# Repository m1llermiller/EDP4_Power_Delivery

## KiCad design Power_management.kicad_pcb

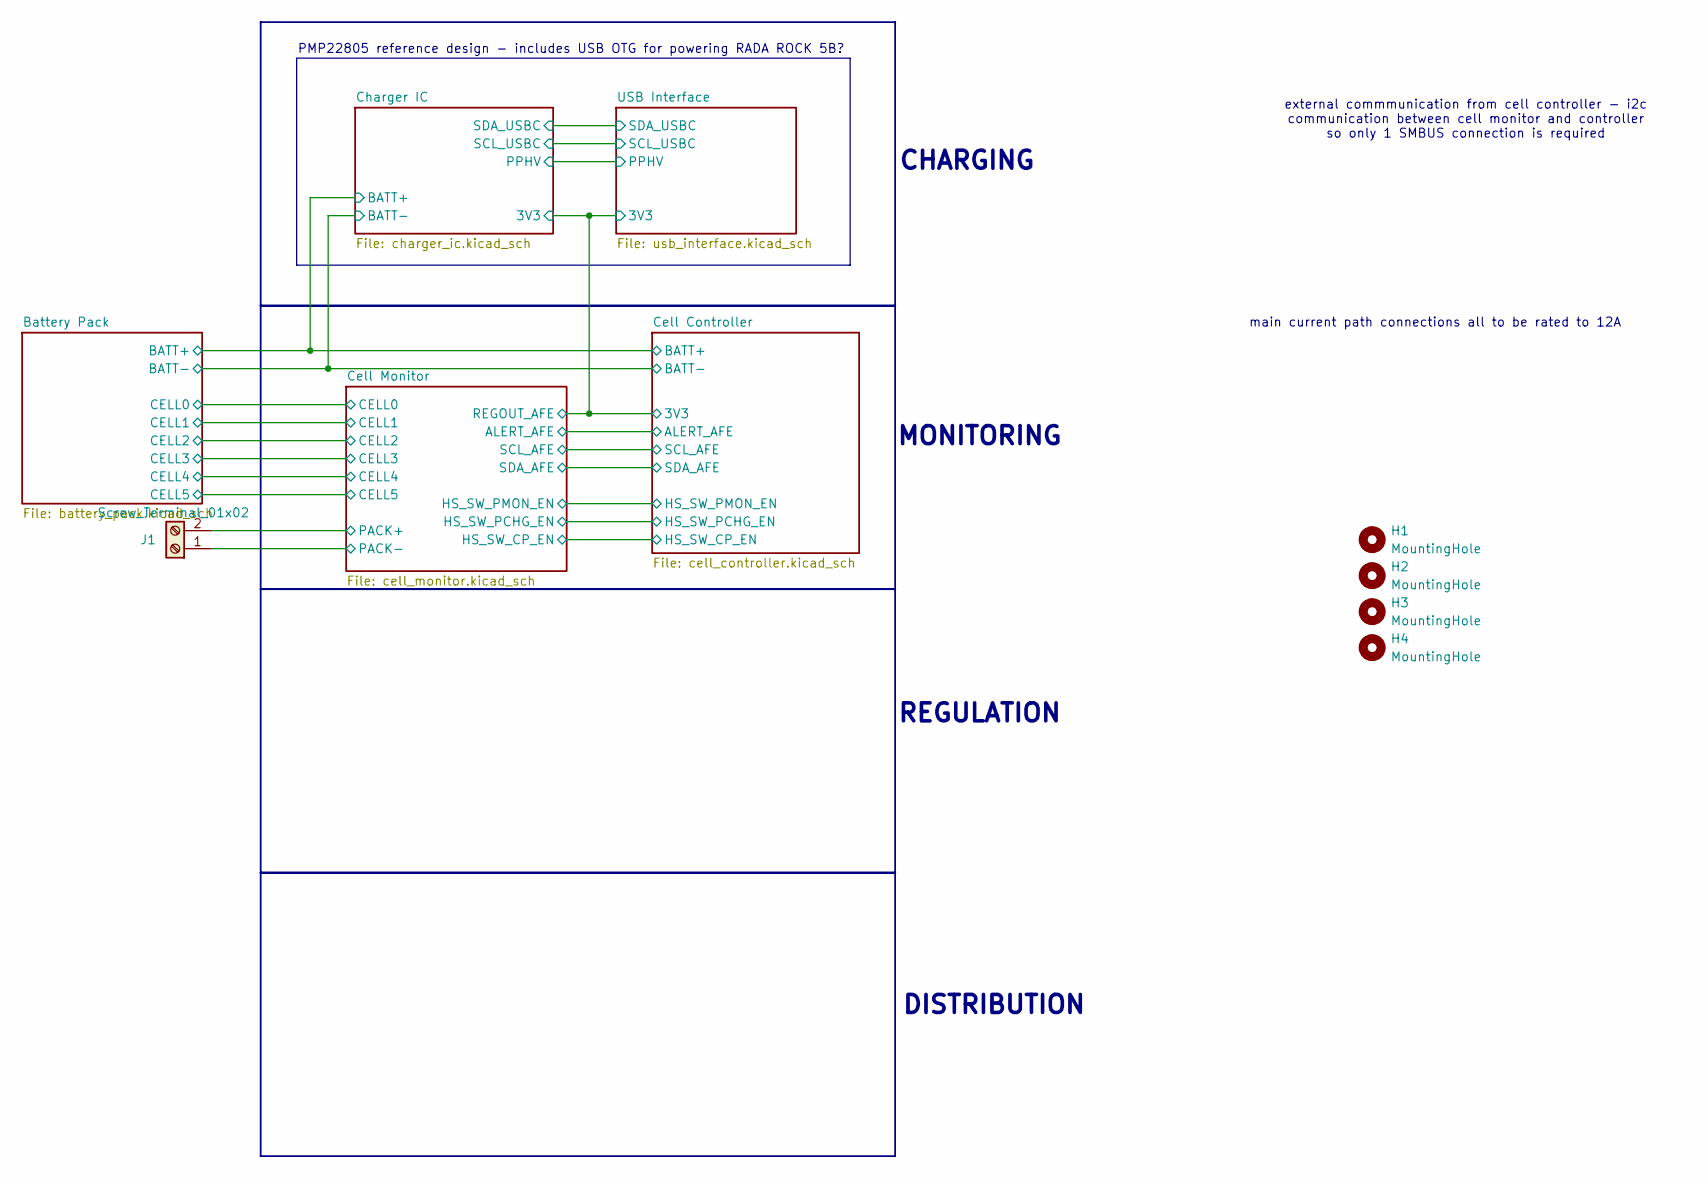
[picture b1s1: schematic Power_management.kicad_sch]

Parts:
H1, H2, H3, H4: MountingHole; MountingHole_3.2mm_M3
J1: Screw_Terminal_01x02; TerminalBlock_Phoenix_MKDS-1,5-2-5.08_1x02_P5.08mm_Horizont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

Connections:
/Cell Monitor/PACK+: J1.2; also elsewhere on the board
/Cell Monitor/PACK-: J1.1; also elsewhere on the board

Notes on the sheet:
external commmunication from cell controller - i2c communication between cell monitor and controller so only 1 SMBUS connection is required
CHARGING
REGULATION
MONITORING
PMP22805 reference design - includes USB OTG for powering RADA ROCK 5B?
DISTRIBUTION
main current path connections all to be rated to 12A

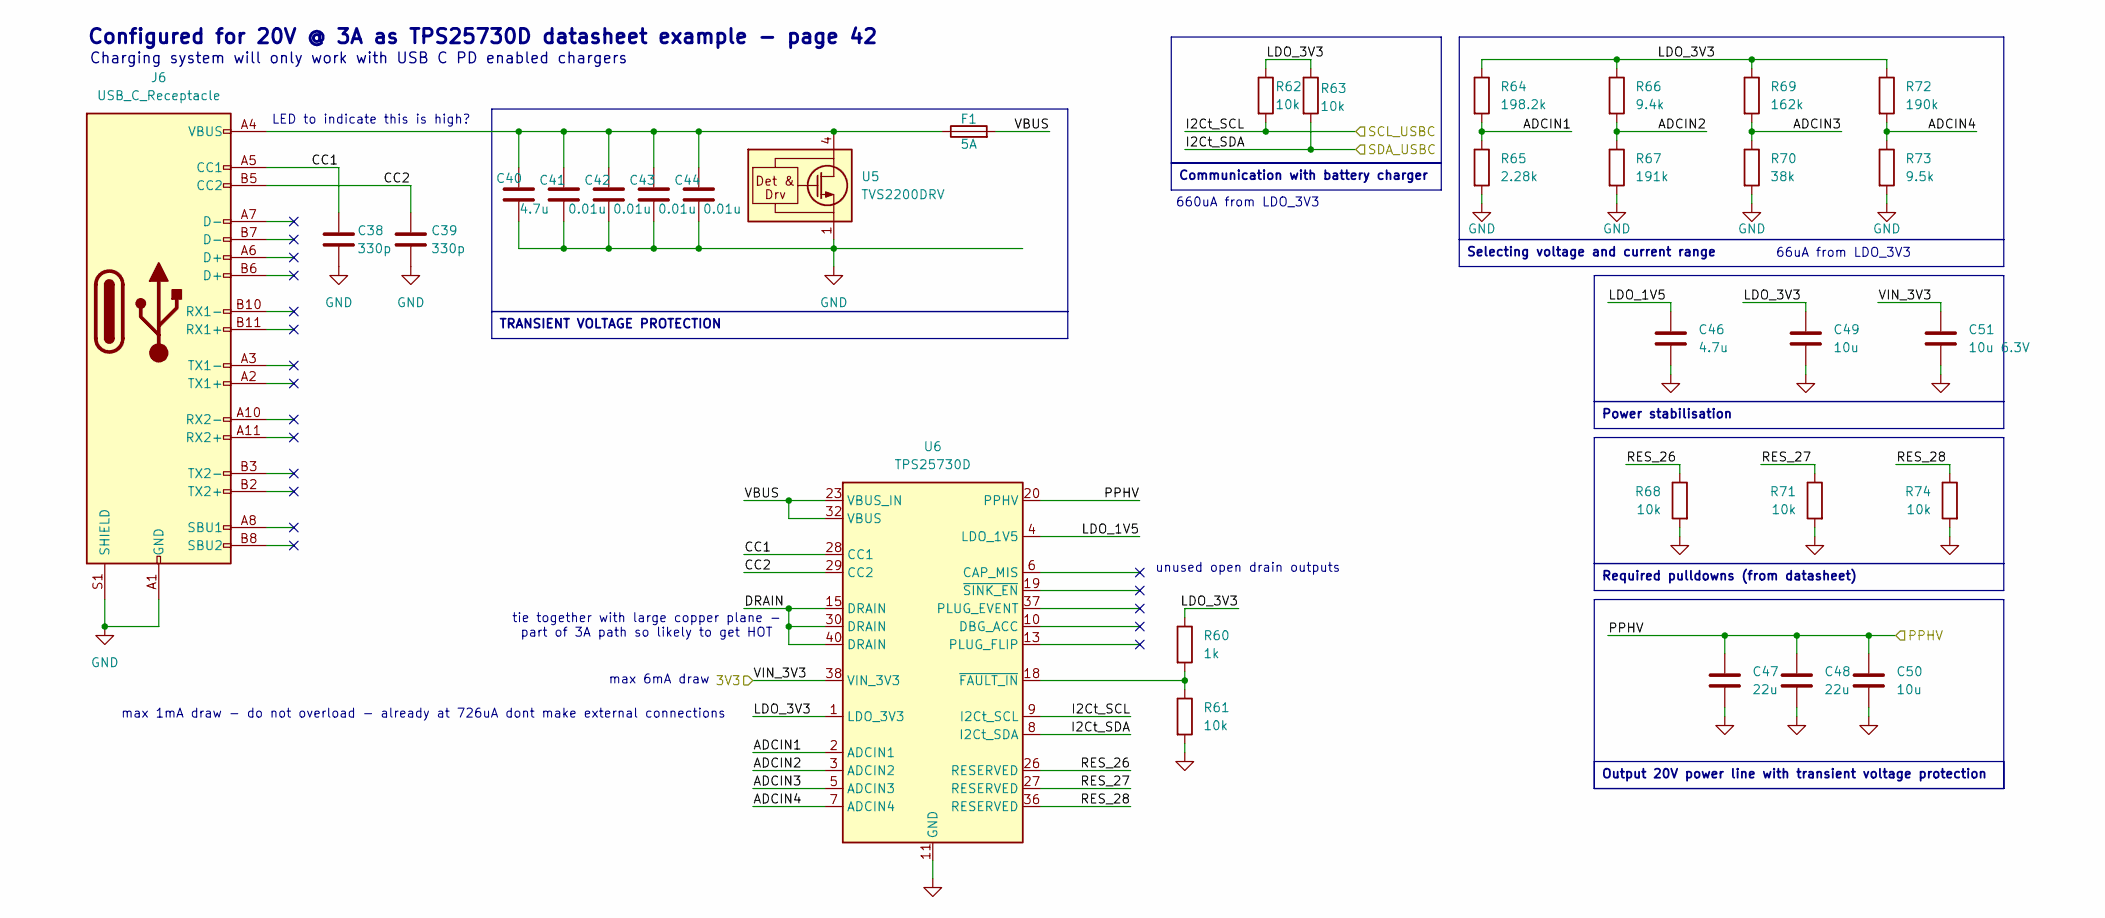
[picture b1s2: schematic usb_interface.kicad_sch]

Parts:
C38, C39: 330p; C_0805_2012Metric_Pad1.18x1.45mm_HandSolder
C40, C46: 4.7u; C_0805_2012Metric_Pad1.18x1.45mm_HandSolder
C41, C42, C43, C44: 0.01u; C_0805_2012Metric_Pad1.18x1.45mm_HandSolder
C47, C48: 22u; C_0805_2012Metric_Pad1.18x1.45mm_HandSolder
C49, C50: 10u; C_0805_2012Metric_Pad1.18x1.45mm_HandSolder
C51: 10u 6.3V; C_0805_2012Metric_Pad1.18x1.45mm_HandSolder
F1: 5A; Fuse_2010_5025Metric
J6: USB_C_Receptacle; USB_C_Receptacle_GCT_USB4135-GF-A_6P_TopMnt_Horizontal
R60: 1k; R_0805_2012Metric_Pad1.20x1.40mm_HandSolder
R61, R62, R63, R68, R71, R74: 10k; R_0805_2012Metric_Pad1.20x1.40mm_HandSolder
R64: 198.2k; R_0805_2012Metric_Pad1.20x1.40mm_HandSolder
R65: 2.28k; R_0805_2012Metric_Pad1.20x1.40mm_HandSolder
R66: 9.4k; R_0805_2012Metric_Pad1.20x1.40mm_HandSolder
R67: 191k; R_0805_2012Metric_Pad1.20x1.40mm_HandSolder
R69: 162k; R_0805_2012Metric_Pad1.20x1.40mm_HandSolder
R70: 38k; R_0805_2012Metric_Pad1.20x1.40mm_HandSolder
R72: 190k; R_0805_2012Metric_Pad1.20x1.40mm_HandSolder
R73: 9.5k; R_0805_2012Metric_Pad1.20x1.40mm_HandSolder
U5: TVS2200DRV; WSON-6-1EP_2x2mm_P0.65mm_EP1x1.6mm
U6: TPS25730D; Texas_REF0038A_WQFN-38-2EP_6x4mm_P0.4

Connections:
+3V3: C51.1, U6.38 (VIN_3V3); also elsewhere on the board
/USB Interface/ADCIN1: R64.2, R65.1, U6.2 (ADCIN1)
/USB Interface/ADCIN2: R66.2, R67.1, U6.3 (ADCIN2)
/USB Interface/ADCIN3: R69.2, R70.1, U6.5 (ADCIN3)
/USB Interface/ADCIN4: R72.2, R73.1, U6.7 (ADCIN4)
/USB Interface/CC1: C38.1, J6.A5 (CC1), U6.28 (CC1)
/USB Interface/CC2: C39.1, J6.B5 (CC2), U6.29 (CC2)
/USB Interface/DRAIN: U6.15 (DRAIN), U6.30 (DRAIN), U6.40 (DRAIN)
/USB Interface/I2Ct_SCL: R62.2, U6.9 (I2Ct_SCL)
/USB Interface/I2Ct_SDA: R63.2, U6.8 (I2Ct_SDA)
/USB Interface/LDO_1V5: C46.1, U6.4 (LDO_1V5)
/USB Interface/LDO_3V3: C49.1, R60.1, R62.1, R63.1, R64.1, R66.1, R69.1, R72.1, U6.1 (LDO_3V3)
/USB Interface/PPHV: C47.1, C48.1, C50.1, U6.20 (PPHV); also elsewhere on the board
/USB Interface/RES_26: R68.1, U6.26 (RESERVED)
/USB Interface/RES_27: R71.1, U6.27 (RESERVED)
/USB Interface/RES_28: R74.1, U6.36 (RESERVED)
/USB Interface/VBUS: F1.2, U6.23 (VBUS_IN), U6.32 (VBUS)
GND: C38.2, C39.2, C40.2, C41.2, C42.2, C43.2, C44.2, C46.2, C47.2, C48.2, C49.2, C50.2, C51.2, J6.A1 (GND), J6.A12 (GND), J6.B1 (GND), J6.B12 (GND), J6.S1 (SHIELD), R61.2, R65.2, R67.2, R68.2, R70.2, R71.2, R73.2, R74.2, U5.1 (GND), U5.2 (GND), U5.3 (GND), U5.7 (GND), U6.11 (GND), U6.12 (GND), U6.14 (GND), U6.16 (GND), U6.17 (GND), U6.31 (GND), U6.34 (GND), U6.39 (GND); also elsewhere on the board
unnamed: C40.1, C41.1, C42.1, C43.1, C44.1, F1.1, J6.A4 (VBUS), J6.A9 (VBUS), J6.B4 (VBUS), J6.B9 (VBUS), U5.4 (IN), U5.5 (IN), U5.6 (IN)
unnamed: R60.2, R61.1, U6.18 (~FAULT_IN)

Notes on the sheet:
tie together with large copper plane - part of 3A path so likely to get HOT
max 1mA draw - do not overload - already at 726uA dont make external connections
Configured for 20V @ 3A as TPS25730D datasheet example - page 42
LED to indicate this is high?
66uA from LDO_3V3
unused open drain outputs
660uA from LDO_3V3
max 6mA draw
Charging system will only work with USB C PD enabled chargers
TRANSIENT VOLTAGE PROTECTION
Output 20V power line with transient voltage protection
Communication with battery charger
Selecting voltage and current range
Power stabilisation
Required pulldowns (from datasheet)

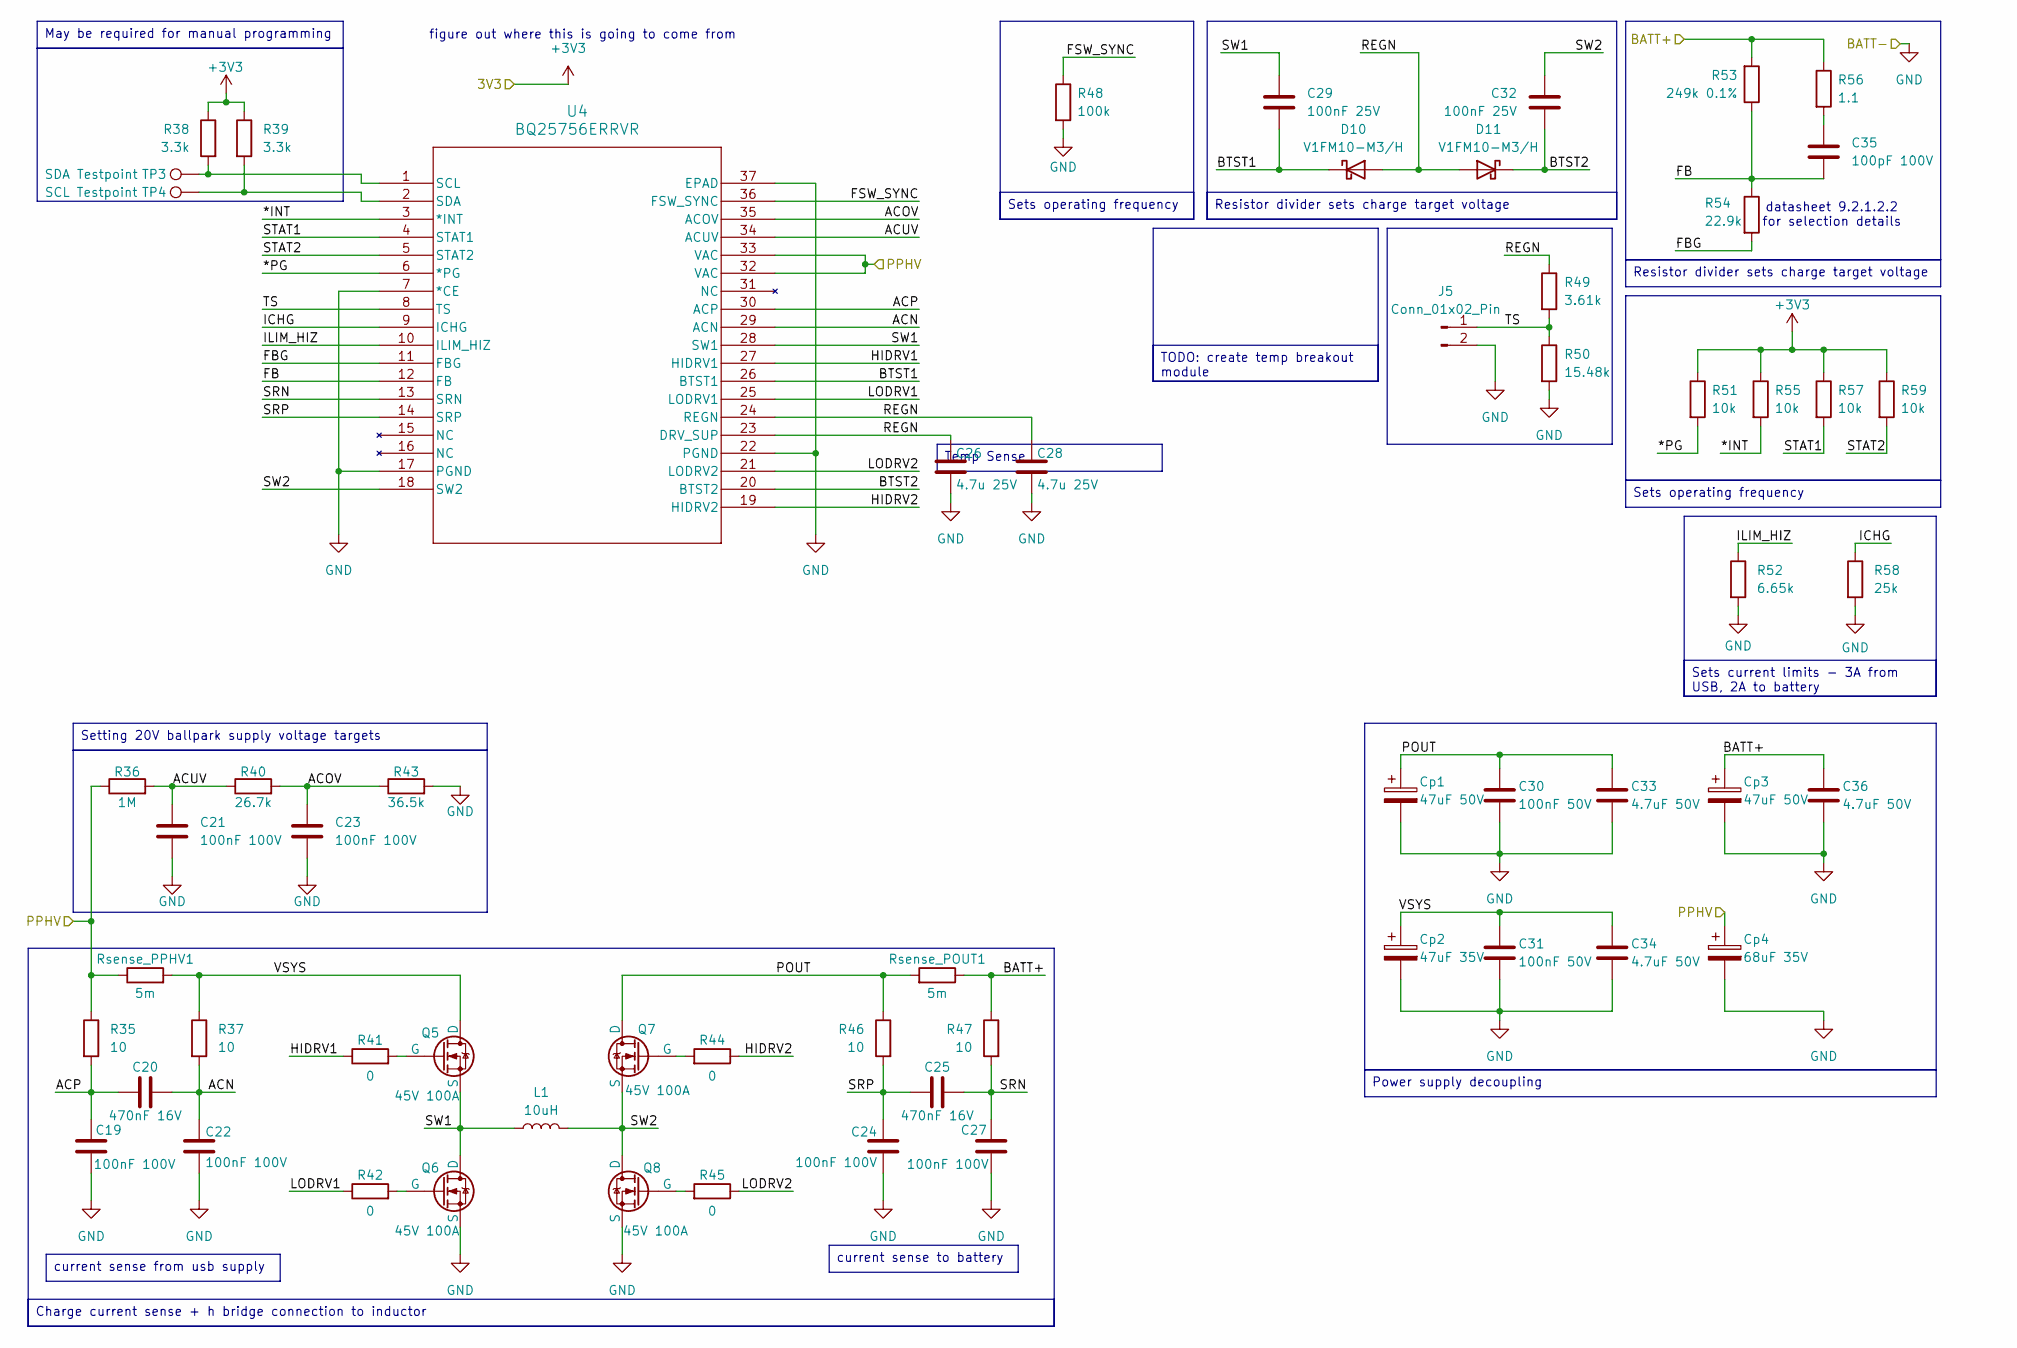
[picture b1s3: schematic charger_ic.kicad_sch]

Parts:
C19, C21, C22, C23, C24, C27: 100nF 100V; C_0805_2012Metric_Pad1.18x1.45mm_HandSolder
C20, C25: 470nF 16V; C_0805_2012Metric_Pad1.18x1.45mm_HandSolder
C26, C28: 4.7u 25V; C_0805_2012Metric_Pad1.18x1.45mm_HandSolder
C29, C32: 100nF 25V; C_0805_2012Metric_Pad1.18x1.45mm_HandSolder
C30, C31: 100nF 50V; C_0805_2012Metric_Pad1.18x1.45mm_HandSolder
C33, C34, C36: 4.7uF 50V; C_0805_2012Metric_Pad1.18x1.45mm_HandSolder
C35: 100pF 100V; C_0805_2012Metric_Pad1.18x1.45mm_HandSolder
Cp1, Cp3: 47uF 50V; CP_Radial_D6.3mm_P2.50mm
Cp2: 47uF 35V; CP_Radial_D6.3mm_P2.50mm
Cp4: 68uF 35V; CP_Radial_D6.3mm_P2.50mm
D10, D11: V1FM10-M3/H; D_SMF
J5: Conn_01x02_Pin; PinHeader_1x02_P2.54mm_Vertical
L1: 10uH; L_APV_APH1240
Q5, Q6, Q7, Q8: 45V 100A; Vishay_PowerPAK_1212-8_Single
R35, R37, R46, R47: 10; R_0805_2012Metric_Pad1.20x1.40mm_HandSolder
R36: 1M; R_0805_2012Metric_Pad1.20x1.40mm_HandSolder
R38, R39: 3.3k; R_0805_2012Metric_Pad1.20x1.40mm_HandSolder
R40: 26.7k; R_0805_2012Metric_Pad1.20x1.40mm_HandSolder
R41, R42, R44, R45: 0; R_0805_2012Metric_Pad1.20x1.40mm_HandSolder
R43: 36.5k; R_0805_2012Metric_Pad1.20x1.40mm_HandSolder
R48: 100k; R_0805_2012Metric_Pad1.20x1.40mm_HandSolder
R49: 3.61k; R_0805_2012Metric_Pad1.20x1.40mm_HandSolder
R50: 15.48k; R_0805_2012Metric_Pad1.20x1.40mm_HandSolder
R51, R55, R57, R59: 10k; R_0805_2012Metric_Pad1.20x1.40mm_HandSolder
R52: 6.65k; R_0805_2012Metric_Pad1.20x1.40mm_HandSolder
R53: 249k 0.1%; R_0805_2012Metric_Pad1.20x1.40mm_HandSolder
R54: 22.9k; R_0805_2012Metric_Pad1.20x1.40mm_HandSolder
R56: 1.1; R_0805_2012Metric_Pad1.20x1.40mm_HandSolder
R58: 25k; R_0805_2012Metric_Pad1.20x1.40mm_HandSolder
Rsense_POUT1: 5m; R_0805_2012Metric_Pad1.20x1.40mm_HandSolder
Rsense_PPHV1: 5m; R_0805_2012Metric_Pad1.20x1.40mm_HandSolder
TP3: SDA Testpoint; TestPoint_Keystone_5005-5009_Compact
TP4: SCL Testpoint; TestPoint_Keystone_5005-5009_Compact
U4: BQ25756ERRVR; VQFN36_RRV_TEX

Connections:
+3V3: R38.1, R39.1, R51.1, R55.1, R57.1, R59.1; also elsewhere on the board
/Cell Monitor/Top_cell_stack: C36.1, Cp3.1, R47.1, R53.2, R56.1, Rsense_POUT1.1; also elsewhere on the board
/Charger IC/*INT: R55.2, U4.3 (*INT)
/Charger IC/*PG: R51.2, U4.6 (*PG)
/Charger IC/ACN: C20.2, C22.1, R37.2, U4.29 (ACN)
/Charger IC/ACOV: C23.1, R40.2, R43.1, U4.35 (ACOV)
/Charger IC/ACP: C19.1, C20.1, R35.2, U4.30 (ACP)
/Charger IC/ACUV: C21.1, R36.2, R40.1, U4.34 (ACUV)
/Charger IC/BTST1: C29.1, D10.1 (K), U4.26 (BTST1)
/Charger IC/BTST2: C32.1, D11.1 (K), U4.20 (BTST2)
/Charger IC/FB: C35.2, R53.1, R54.1, U4.12 (FB)
/Charger IC/FBG: R54.2, U4.11 (FBG)
/Charger IC/FSW_SYNC: R48.1, U4.36 (FSW_SYNC)
/Charger IC/HIDRV1: R41.1, U4.27 (HIDRV1)
/Charger IC/HIDRV2: R44.1, U4.19 (HIDRV2)
/Charger IC/ICHG: R58.1, U4.9 (ICHG)
/Charger IC/ILIM_HIZ: R52.1, U4.10 (ILIM_HIZ)
/Charger IC/LODRV1: R42.1, U4.25 (LODRV1)
/Charger IC/LODRV2: R45.1, U4.21 (LODRV2)
/Charger IC/POUT: C30.1, C33.1, Cp1.1, Q7.1 (D), R46.1, Rsense_POUT1.2
/Charger IC/REGN: C26.1, C28.1, D10.2 (A), D11.2 (A), R49.1, U4.23 (DRV_SUP), U4.24 (REGN)
/Charger IC/SRN: C25.1, C27.1, R47.2, U4.13 (SRN)
/Charger IC/SRP: C24.1, C25.2, R46.2, U4.14 (SRP)
/Charger IC/STAT1: R57.2, U4.4 (STAT1)
/Charger IC/STAT2: R59.2, U4.5 (STAT2)
/Charger IC/SW1: C29.2, L1.1, Q5.3 (S), Q6.1 (D), U4.28 (SW1)
/Charger IC/SW2: C32.2, L1.2, Q7.3 (S), Q8.1 (D), U4.18 (SW2)
/Charger IC/TS: J5.1, R49.2, R50.1, U4.8 (TS)
/Charger IC/VSYS: C31.1, C34.1, Cp2.1, Q5.1 (D), R37.1, Rsense_PPHV1.2
/USB Interface/PPHV: Cp4.1, R35.1, R36.1, Rsense_PPHV1.1, U4.32 (VAC), U4.33 (VAC); also elsewhere on the board
GND: C19.2, C21.2, C22.2, C23.2, C24.2, C26.2, C27.2, C28.2, C30.2, C31.2, C33.2, C34.2, C36.2, Cp1.2, Cp2.2, Cp3.2, Cp4.2, J5.2, Q6.3 (S), Q8.3 (S), R43.2, R48.2, R50.2, R52.2, R58.2, U4.7 (*CE), U4.17 (PGND), U4.22 (PGND), U4.37 (EPAD); also elsewhere on the board
unnamed: C35.1, R56.2
unnamed: Q5.2 (G), R41.2
unnamed: Q6.2 (G), R42.2
unnamed: Q7.2 (G), R44.2
unnamed: Q8.2 (G), R45.2
unnamed: R38.2, TP3.1 (1_1), U4.1 (SCL)
unnamed: R39.2, TP4.1 (1_1), U4.2 (SDA)

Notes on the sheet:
datasheet 9.2.1.2.2 for selection details
figure out where this is going to come from
Temp Sense
Resistor divider sets charge target voltage
Sets operating frequency
May be required for manual programming
current sense from usb supply
current sense to battery
Setting 20V ballpark supply voltage targets
Power supply decoupling
Sets current limits - 3A from USB, 2A to battery
Charge current sense + h bridge connection to inductor
TODO: create temp breakout module

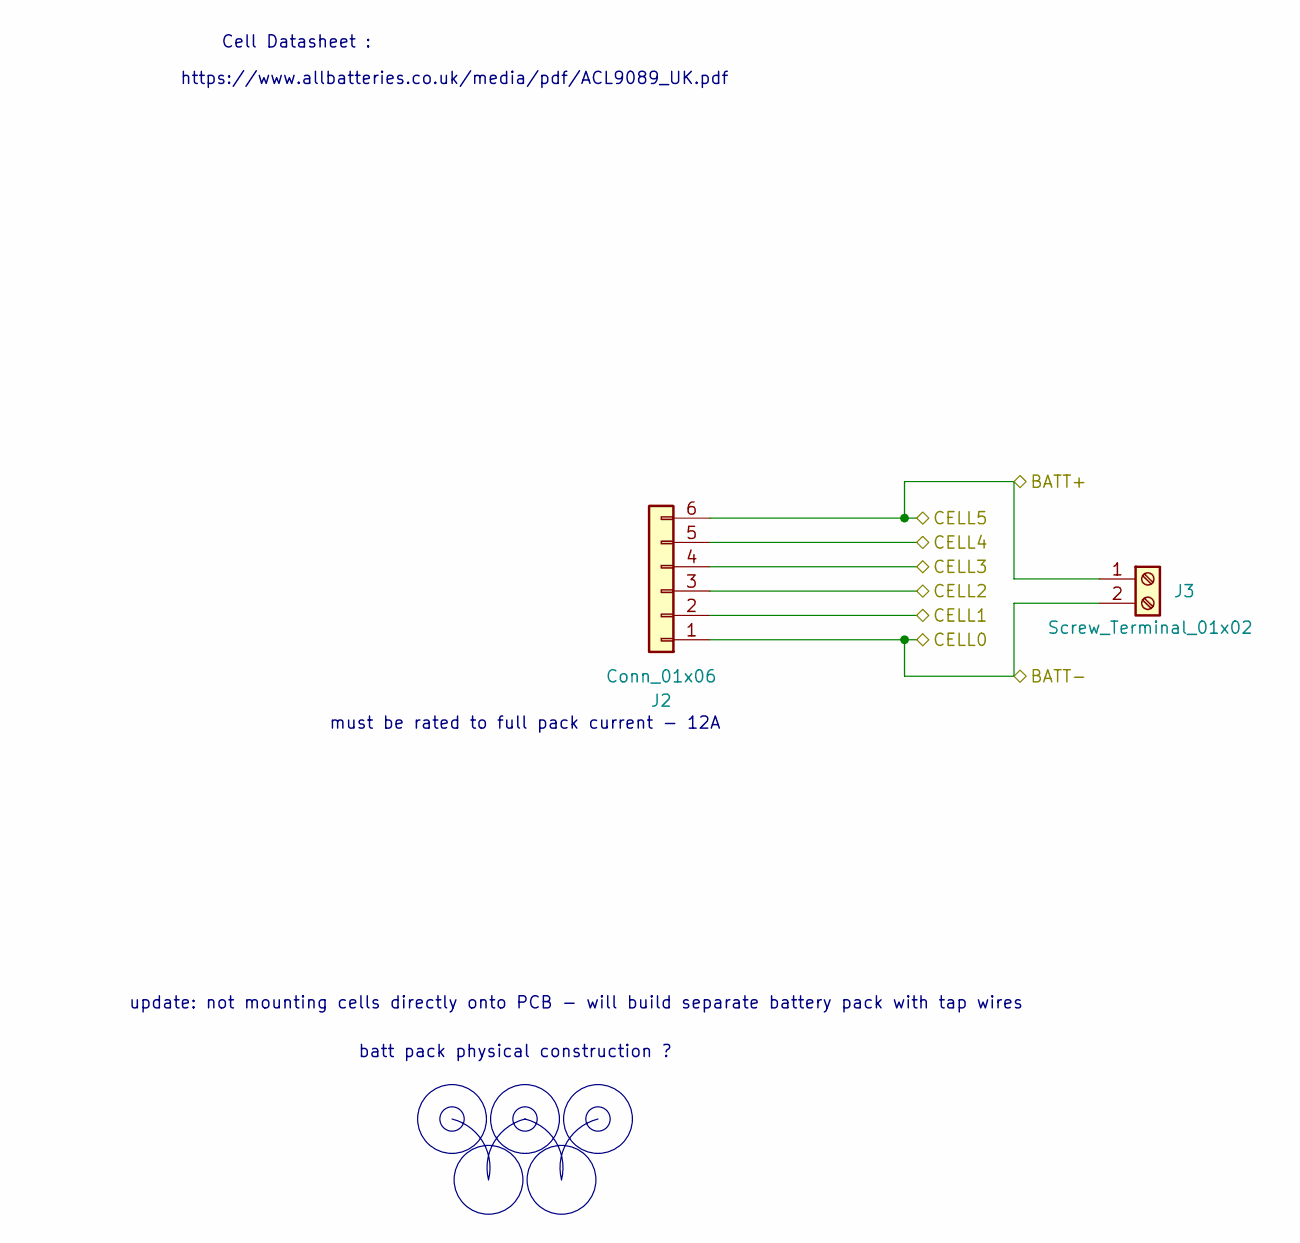
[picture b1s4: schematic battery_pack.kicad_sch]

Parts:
J2: Conn_01x06; PinHeader_1x06_P2.54mm_Horizontal
J3: Screw_Terminal_01x02; TerminalBlock_Phoenix_MKDS-1,5-2-5.08_1x02_P5.08mm_Horizont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

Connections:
/Battery Pack/CELL2: J2.3; also elsewhere on the board
/Battery Pack/CELL3: J2.4; also elsewhere on the board
/Battery Pack/CELL4: J2.5; also elsewhere on the board
/Cell Monitor/Cell_one: J2.2; also elsewhere on the board
/Cell Monitor/Top_cell_stack: J2.6, J3.1; also elsewhere on the board
GND: J2.1, J3.2; also elsewhere on the board

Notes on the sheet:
must be rated to full pack current - 12A
https://www.allbatteries.co.uk/media/pdf/ACL9089_UK.pdf
batt pack physical construction ?
update: not mounting cells directly onto PCB - will build separate battery pack with tap wires
Cell Datasheet :

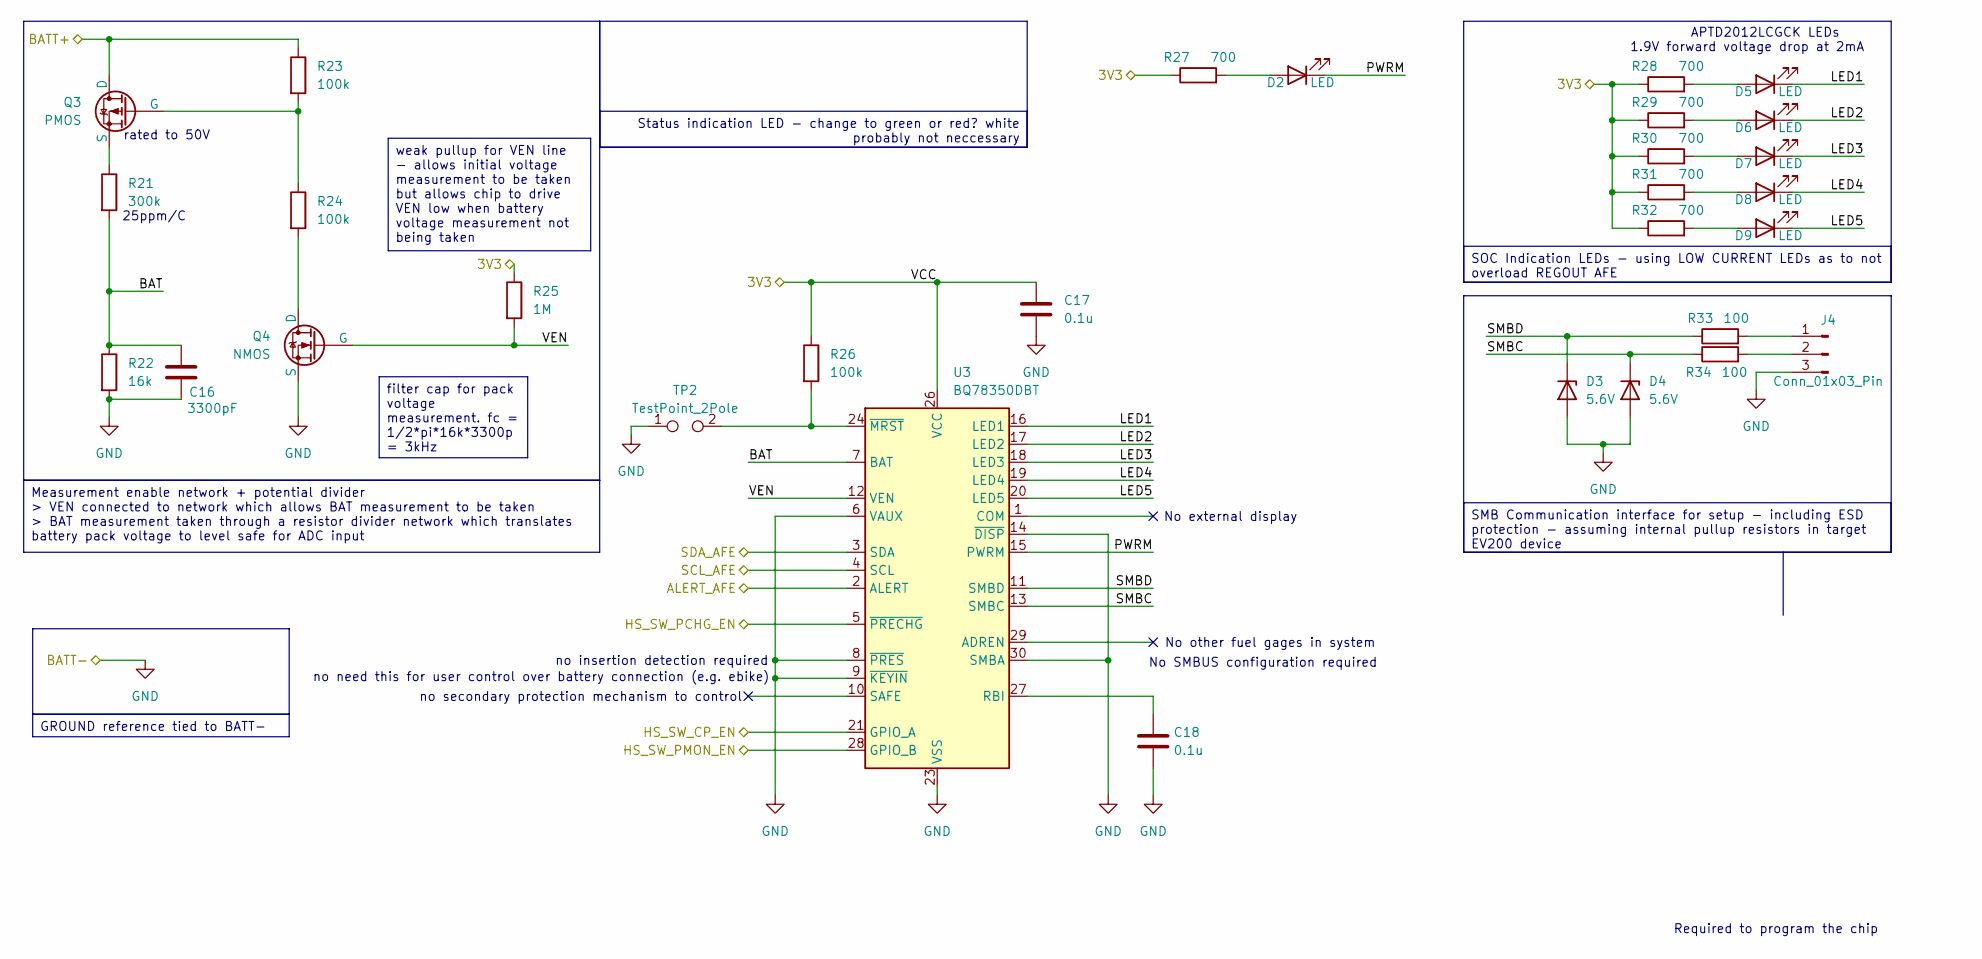
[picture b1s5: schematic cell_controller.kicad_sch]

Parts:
C16: 3300pF; C_0805_2012Metric_Pad1.18x1.45mm_HandSolder
C17, C18: 0.1u; C_0805_2012Metric_Pad1.18x1.45mm_HandSolder
D2, D5, D6, D7, D8, D9: LED; LED_0805_2012Metric_Pad1.15x1.40mm_HandSolder
D3, D4: 5.6V; D_0805_2012Metric_Pad1.15x1.40mm_HandSolder
J4: Conn_01x03_Pin; PinHeader_1x03_P2.54mm_Vertical
Q3: PMOS; SOT-23_Handsoldering
Q4: NMOS; SOT-23_Handsoldering
R21: 300k; R_0805_2012Metric_Pad1.20x1.40mm_HandSolder
R22: 16k; R_0805_2012Metric_Pad1.20x1.40mm_HandSolder
R23, R24, R26: 100k; R_0805_2012Metric_Pad1.20x1.40mm_HandSolder
R25: 1M; R_0805_2012Metric_Pad1.20x1.40mm_HandSolder
R27, R28, R29, R30, R31, R32: 700; R_0805_2012Metric_Pad1.20x1.40mm_HandSolder
R33, R34: 100; R_0805_2012Metric_Pad1.20x1.40mm_HandSolder
TP2: TestPoint_2Pole; SolderJumper-2_P1.3mm_Open_RoundedPad1.0x1.5mm
U3: BQ78350DBT; TSSOP-30_4.4x7.8mm_P0.5mm

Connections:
+3V3: C17.1, R25.1, R26.1, R27.1, R28.1, R29.1, R30.1, R31.1, R32.1, U3.26 (VCC); also elsewhere on the board
/Cell Controller/BAT: C16.1, R21.2, R22.1, U3.7 (BAT)
/Cell Controller/HS_SW_CP_EN: U3.21 (GPIO_A); also elsewhere on the board
/Cell Controller/HS_SW_PCHG_EN: U3.5 (~PRECHG); also elsewhere on the board
/Cell Controller/HS_SW_PMON_EN: U3.28 (GPIO_B); also elsewhere on the board
/Cell Controller/LED1: D5.1 (K), U3.16 (LED1)
/Cell Controller/LED2: D6.1 (K), U3.17 (LED2)
/Cell Controller/LED3: D7.1 (K), U3.18 (LED3)
/Cell Controller/LED4: D8.1 (K), U3.19 (LED4)
/Cell Controller/LED5: D9.1 (K), U3.20 (LED5)
/Cell Controller/PWRM: D2.1 (K), U3.15 (PWRM)
/Cell Controller/SMBC: D4.1 (K), R34.1, U3.13 (SMBC)
/Cell Controller/SMBD: D3.1 (K), R33.1, U3.11 (SMBD)
/Cell Controller/VEN: Q4.2 (G), R25.2, U3.12 (VEN)
/Cell Monitor/ALERT_AFE: U3.2 (ALERT); also elsewhere on the board
/Cell Monitor/SCL_AFE: U3.4 (SCL); also elsewhere on the board
/Cell Monitor/SDA_AFE: U3.3 (SDA); also elsewhere on the board
/Cell Monitor/Top_cell_stack: Q3.1 (D), R23.1; also elsewhere on the board
GND: C16.2, C17.2, C18.2, D3.2 (A), D4.2 (A), J4.3, Q4.3 (S), R22.2, TP2.1, U3.6 (VAUX), U3.8 (~PRES), U3.9 (~KEYIN), U3.14 (~DISP), U3.22 (VSS), U3.23 (VSS), U3.25 (VSS), U3.30 (SMBA); also elsewhere on the board
unnamed: D2.2 (A), R27.2
unnamed: D5.2 (A), R28.2
unnamed: D6.2 (A), R29.2
unnamed: D7.2 (A), R30.2
unnamed: D8.2 (A), R31.2
unnamed: D9.2 (A), R32.2
unnamed: J4.1, R33.2
unnamed: J4.2, R34.2
unnamed: Q3.2 (G), R23.2, R24.1
unnamed: Q3.3 (S), R21.1
unnamed: Q4.1 (D), R24.2
unnamed: C18.1, U3.27 (RBI)
unnamed: R26.2, TP2.2, U3.24 (~MRST)

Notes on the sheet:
No other fuel gages in system
APTD2012LCGCK LEDs
rated to 50V
no need this for user control over battery connection (e.g. ebike)
No SMBUS configuration required
1.9V forward voltage drop at 2mA
no insertion detection required
No external display
25ppm/C
Required to program the chip
no secondary protection mechanism to control
SOC Indication LEDs - using LOW CURRENT LEDs as to not overload REGOUT AFE
SMB Communication interface for setup - including ESD protection - assuming internal pullup resistors in target EV200 device
Status indication LED - change to green or red? white probably not neccessary
GROUND reference tied to BATT-
filter cap for pack voltage measurement. fc = 1/2*pi*16k*3300p = 3kHz
weak pullup for VEN line - allows initial voltage measurement to be taken but allows chip to drive VEN low when battery voltage measurement not being taken
Measurement enable network + potential divider > VEN connected to network which allows BAT measurement to be taken > BAT measurement taken through a resistor divider network which translates battery pack voltage to level safe for ADC input

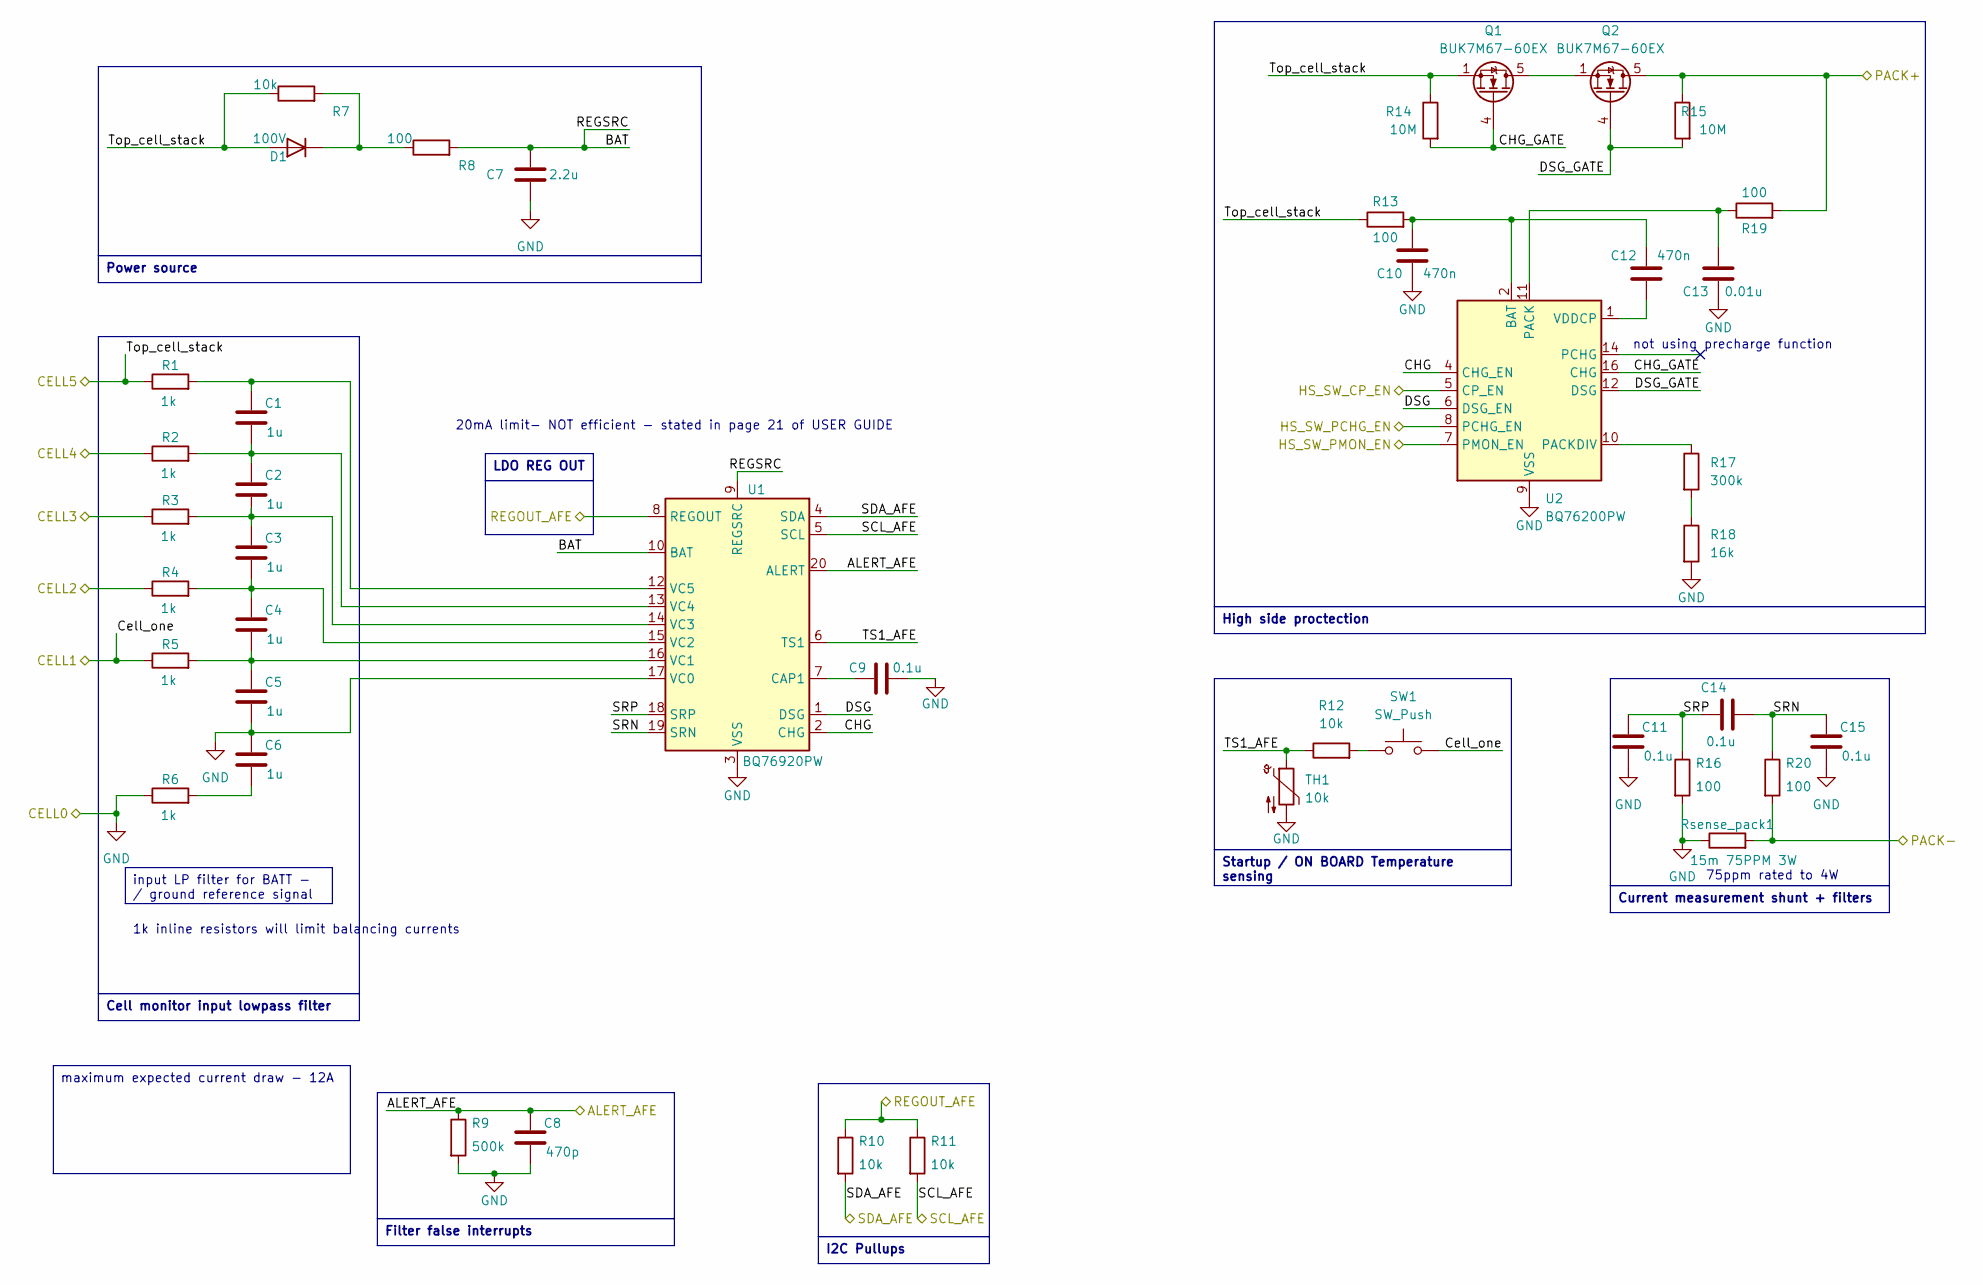
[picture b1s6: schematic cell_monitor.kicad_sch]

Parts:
C1, C2, C3, C4, C5, C6: 1u; C_0805_2012Metric_Pad1.18x1.45mm_HandSolder
C7: 2.2u; C_0805_2012Metric_Pad1.18x1.45mm_HandSolder
C8: 470p; C_0805_2012Metric_Pad1.18x1.45mm_HandSolder
C9, C11, C14, C15: 0.1u; C_0805_2012Metric_Pad1.18x1.45mm_HandSolder
C10, C12: 470n; C_0805_2012Metric_Pad1.18x1.45mm_HandSolder
C13: 0.01u; C_0805_2012Metric_Pad1.18x1.45mm_HandSolder
D1: 100V; D_0805_2012Metric_Pad1.15x1.40mm_HandSolder
Q1, Q2: BUK7M67-60EX; LFPAK33
R1, R2, R3, R4, R5, R6: 1k; R_0805_2012Metric_Pad1.20x1.40mm_HandSolder
R7, R10, R11, R12: 10k; R_0805_2012Metric_Pad1.20x1.40mm_HandSolder
R8, R13, R16, R19, R20: 100; R_0805_2012Metric_Pad1.20x1.40mm_HandSolder
R9: 500k; R_0805_2012Metric_Pad1.20x1.40mm_HandSolder
R14, R15: 10M; R_0805_2012Metric_Pad1.20x1.40mm_HandSolder
R17: 300k; R_0805_2012Metric_Pad1.20x1.40mm_HandSolder
R18: 16k; R_0805_2012Metric_Pad1.20x1.40mm_HandSolder
Rsense_pack1: 15m 75PPM 3W; RESM11569X253N
SW1: SW_Push; SW_SPST_PTS647_Sx38
TH1: 10k; R_0805_2012Metric_Pad1.20x1.40mm_HandSolder
U1: BQ76920PW; TSSOP-20_4.4x6.5mm_P0.65mm
U2: BQ76200PW; TSSOP-16_4.4x5mm_P0.65mm

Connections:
+3V3: R10.1, R11.1, U1.8 (REGOUT); also elsewhere on the board
/Battery Pack/CELL2: R4.1; also elsewhere on the board
/Battery Pack/CELL3: R3.1; also elsewhere on the board
/Battery Pack/CELL4: R2.1; also elsewhere on the board
/Cell Controller/HS_SW_CP_EN: U2.5 (CP_EN); also elsewhere on the board
/Cell Controller/HS_SW_PCHG_EN: U2.8 (PCHG_EN); also elsewhere on the board
/Cell Controller/HS_SW_PMON_EN: U2.7 (PMON_EN); also elsewhere on the board
/Cell Monitor/ALERT_AFE: C8.1, R9.1, U1.20 (ALERT); also elsewhere on the board
/Cell Monitor/BAT: C7.1, R8.2, U1.9 (REGSRC), U1.10 (BAT)
/Cell Monitor/CHG: U1.2 (CHG), U2.4 (CHG_EN)
/Cell Monitor/CHG_GATE: Q1.4 (G), R14.2, U2.16 (CHG)
/Cell Monitor/Cell_one: R5.1, SW1.2; also elsewhere on the board
/Cell Monitor/DSG: U1.1 (DSG), U2.6 (DSG_EN)
/Cell Monitor/DSG_GATE: Q2.4 (G), R15.2, U2.12 (DSG)
/Cell Monitor/PACK+: Q2.5 (D), R15.1, R19.2; also elsewhere on the board
/Cell Monitor/PACK-: R20.2, Rsense_pack1.2; also elsewhere on the board
/Cell Monitor/SCL_AFE: R11.2, U1.5 (SCL); also elsewhere on the board
/Cell Monitor/SDA_AFE: R10.2, U1.4 (SDA); also elsewhere on the board
/Cell Monitor/SRN: C14.2, C15.1, R20.1, U1.19 (SRN)
/Cell Monitor/SRP: C11.1, C14.1, R16.1, U1.18 (SRP)
/Cell Monitor/TS1_AFE: R12.1, TH1.1, U1.6 (TS1)
/Cell Monitor/Top_cell_stack: D1.2 (A), Q1.1 (S), Q1.2 (S), Q1.3 (S), R1.1, R7.1, R13.1, R14.1; also elsewhere on the board
GND: C5.2, C6.1, C7.2, C8.2, C9.2, C10.1, C11.2, C13.1, C15.2, R6.1, R9.2, R16.2, R18.2, Rsense_pack1.1, TH1.2, U1.3 (VSS), U1.17 (VC0), U2.9 (VSS); also elsewhere on the board
unnamed: C6.2, R6.2
unnamed: D1.1 (K), R7.2, R8.1
unnamed: Q1.5 (D), Q2.1 (S), Q2.2 (S), Q2.3 (S)
unnamed: R12.2, SW1.1
unnamed: R17.2, R18.1
unnamed: C9.1, U1.7 (CAP1)
unnamed: C4.2, C5.1, R5.2, U1.16 (VC1)
unnamed: C3.2, C4.1, R4.2, U1.15 (VC2)
unnamed: C2.2, C3.1, R3.2, U1.14 (VC3)
unnamed: C1.2, C2.1, R2.2, U1.13 (VC4)
unnamed: C1.1, R1.2, U1.12 (VC5)
unnamed: C10.2, C12.2, R13.2, U2.2 (BAT)
unnamed: C13.2, R19.1, U2.11 (PACK)
unnamed: R17.1, U2.10 (PACKDIV)
unnamed: C12.1, U2.1 (VDDCP)

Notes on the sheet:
75ppm rated to 4W
20mA limit- NOT efficient - stated in page 21 of USER GUIDE
1k inline resistors will limit balancing currents
not using precharge function
I2C Pullups
High side proctection
LDO REG OUT
Startup / ON BOARD Temperature sensing
maximum expected current draw - 12A
Cell monitor input lowpass filter
Filter false interrupts
Power source
input LP filter for BATT - / ground reference signal
Current measurement shunt + filters
